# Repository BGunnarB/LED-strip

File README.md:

# LED-strip
I created this project in order to control an RGBW-LED strip from OpenHab using MySensors.
It is based on the sketch by @maghac and @DrJeff but I have taken away the Motion Sensor stuff, since I did not need that.

I implemented support for the W-channel as well so colour messages are now 4 words (aabbccdd) in hex format since this is what OpenHab sends.

There is an ALARM mode that slowly fades to reddish-white and back like “I see you”. The RELAX mode can now be programmed to fade between 8 settings, each being a 4 word hex state e.g.

ff000000
00ff0000
0000ff00
000000ff
aa000000
00aa0000
0000aa00
000000aa

These are the messages that can be sent using MySensors API

Message type		Payload		Comment
	
2  V_STATUS			0 : 1		Off: On

3  V_PERCENTAGE		0 - 100		Dimmer value 0 - 100%

41 V_RGBW			90abcdef	Fade to colour RGBW 90 ab cd ef

24 V_VAR1			0 - 2000	Fade speed. Higher number = lower speed

25 V_VAR2			0 : 1 : 2	0=Normal : 1= alarm : 2= relax

26 V_VAR3			naabbccdd	Set row n in the relax matrix to aabbccdd 0 <= n <= 7

The LED-strip is driven on +24V using IRLZ44N MOSFETs
I ordered the PCB from OSHPark. Since the design was done in KiCad I did not have to generate the Gerber files myself but just sent the .kicad_pcb file to them directly.

In the Arduino nano sketch I implemented some input parameter checking as to not receive nasty surprises from strange input.

In the picture of the circuit board the part on the right is just a +24V power unit based on an L200 and the heatsink for that IC.

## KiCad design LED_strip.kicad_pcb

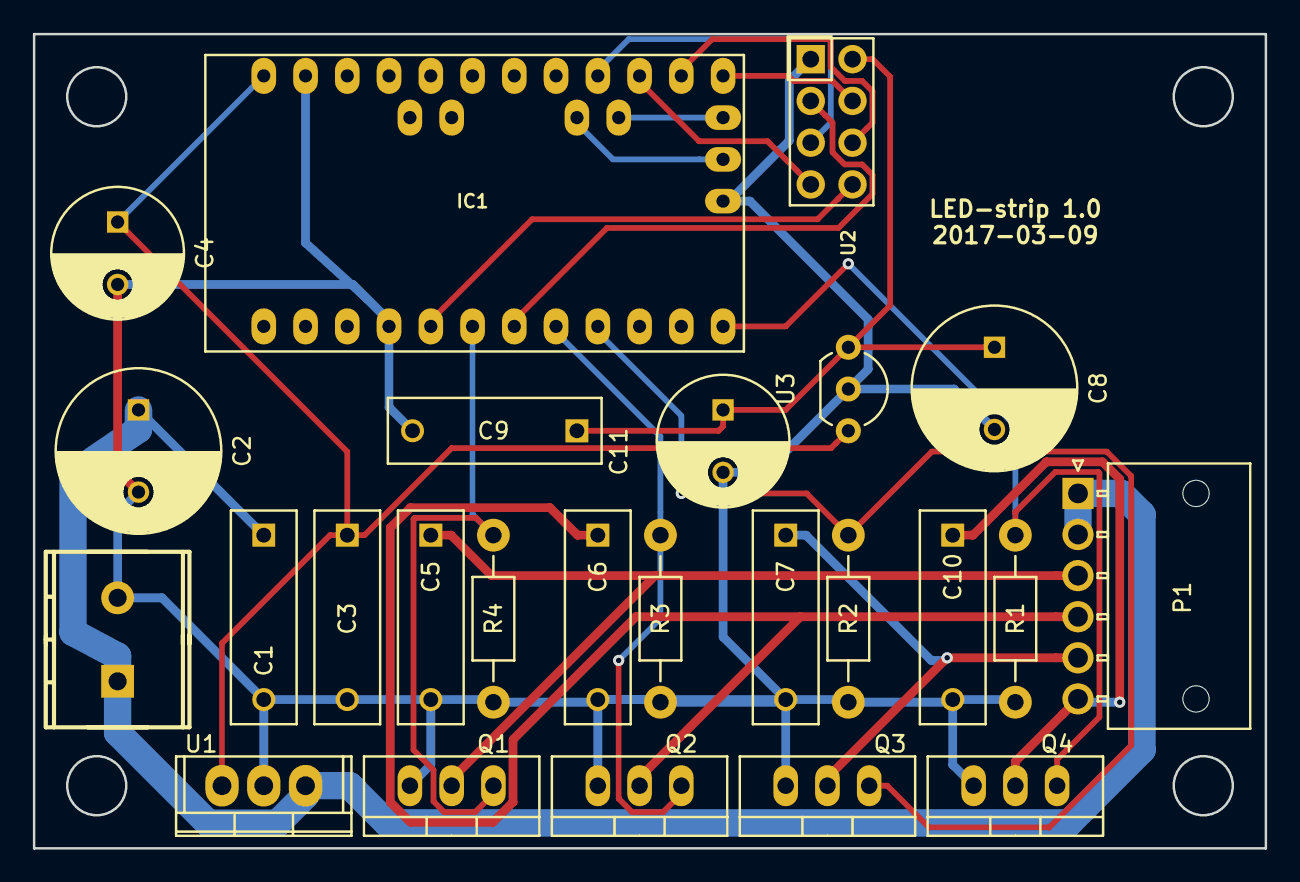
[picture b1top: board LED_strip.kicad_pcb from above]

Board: 2 copper layers, 74.9 x 49.5 mm, 25 parts (0 on the bottom side), 18 nets.

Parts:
C1, C3, C5, C6, C7, C9, C10: 100n; C_Rect_L13_W4_P10
C2: 10u 63V; C_Radial_D10_L13_P5
C4, C11: 22u; C_Radial_D8_L13_P3.8
C8: 10u; C_Radial_D10_L13_P5
IC1: ArduinoProMini; pro_mini
J1: Screw_Terminal_1x02; TerminalBlock2.54mmx2-kcswalter
P1: CONN_01X06; Molex_NanoFit_1x06x2.50mm_Angled
Q1, Q2, Q3, Q4: IRLZ44N; TO-220_Neutral123_Vertical
R1, R2, R3, R4: 2k; Resistor_Horizontal_RM10mm
U1: LM7805CT; TO-220
U2: NRF24L01
U3: LE33ABZ; TO-92_Inline_Wide

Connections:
+24V: C1.1, C2.1, J1.1, P1.1, P1.2, U1.1
/3.3V: C8.1, C9.1, C11.1, U2.2, U3.1
/LED_B: C7.1, P1.5, Q3.2
/LED_G: C6.1, P1.4, Q2.2
/LED_R: C5.1, P1.3, Q1.2
/LED_W: C10.1, P1.6, Q4.2
GND: C1.2, C2.2, C3.2, C4.2, C5.2, C6.2, C7.2, C8.2, C9.2, C10.2, C11.2, IC1.4, IC1.23, IC1.29, J1.2, Q1.3, Q2.3, Q3.3, Q4.3, R1.1, R2.1, R3.1, R4.1, U1.2, U2.1, U3.2
unnamed: C3.1, C4.1, IC1.24, U1.3, U3.3
unnamed: IC1.5, U2.8
unnamed: IC1.6, Q1.1, R4.2
unnamed: IC1.7, U2.3
unnamed: IC1.8, Q2.1, R3.2
unnamed: IC1.9, Q3.1, R2.2
unnamed: IC1.12, Q4.1, R1.2
unnamed: IC1.13, U2.4
unnamed: IC1.14, U2.6
unnamed: IC1.15, U2.7
unnamed: IC1.16, U2.5

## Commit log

2017-10-20 First project description
    This is my first write-up of my project
2017-10-20 Arduino sketch
    The sketch added
2017-10-20 Edits in README.md
    Trying to get linefeeds right
2017-10-20 Changes in README.md
    Still struggling with linefeeds
